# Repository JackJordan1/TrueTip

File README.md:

# TrueTip
Mechanical and electrical design files for the TrueTip hardware. Derivative of the OPEnS eDNA project.

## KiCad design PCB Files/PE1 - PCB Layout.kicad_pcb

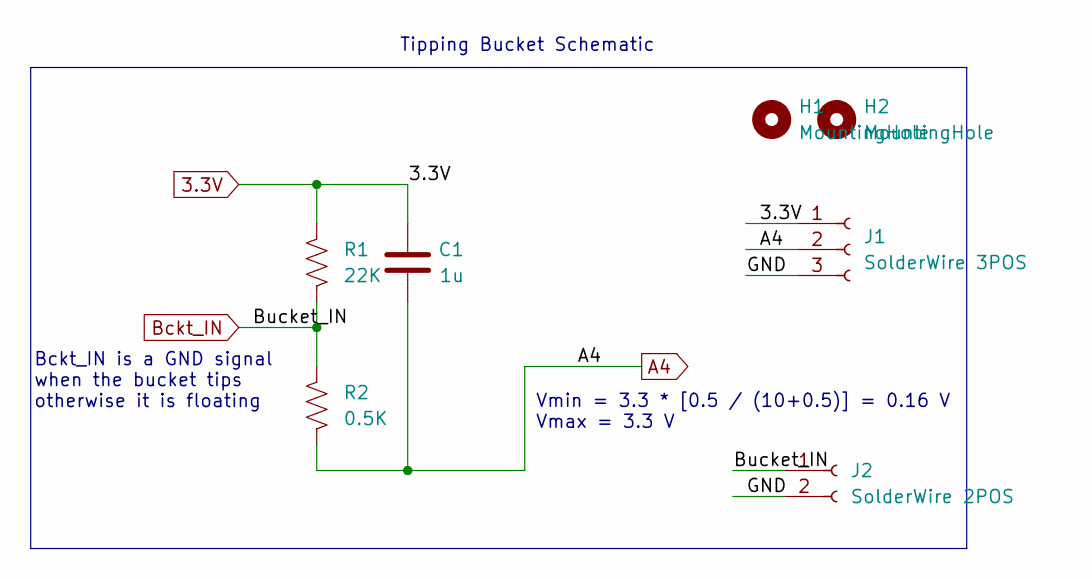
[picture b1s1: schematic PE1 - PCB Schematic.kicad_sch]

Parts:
C1: 1u; C_0805_2012Metric_Pad1.18x1.45mm_HandSolder
H1, H2: MountingHole; MountingHole_3.2mm_M3
J1: SolderWire 3POS; SolderWire-0.1sqmm_1x03_P3.6mm_D0.4mm_OD1mm
J2: SolderWire 2POS; SolderWire-0.1sqmm_1x02_P3.6mm_D0.4mm_OD1mm
R1: 22K; R_0805_2012Metric_Pad1.20x1.40mm_HandSolder
R2: 0.5K; R_0805_2012Metric_Pad1.20x1.40mm_HandSolder

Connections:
3.3V: C1.1, J1.1, R1.1
/GND: J1.3, J2.2
A4: C1.2, J1.2, R2.2
Bckt_IN: J2.1, R1.2, R2.1

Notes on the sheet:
Vmin = 3.3 * [0.5 / (10+0.5)] = 0.16 V Vmax = 3.3 V
Bckt_IN is a GND signal when the bucket tips otherwise it is floating
Tipping Bucket Schematic

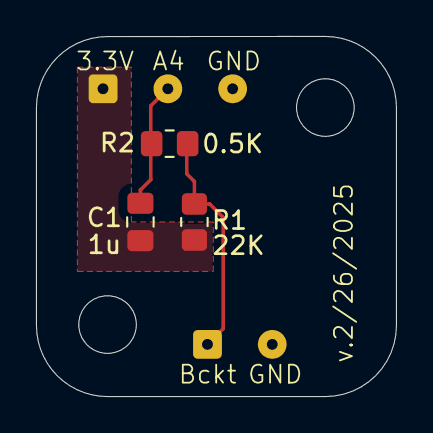
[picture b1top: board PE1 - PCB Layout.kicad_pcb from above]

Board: 2 copper layers, 20.0 x 20.0 mm, 7 parts (0 on the bottom side), 4 nets.

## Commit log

2025-10-06 Uploaded PCB files
2025-10-06 Upload PCB files
2025-12-29 Initial commit (use Git LFS for CAD files)
